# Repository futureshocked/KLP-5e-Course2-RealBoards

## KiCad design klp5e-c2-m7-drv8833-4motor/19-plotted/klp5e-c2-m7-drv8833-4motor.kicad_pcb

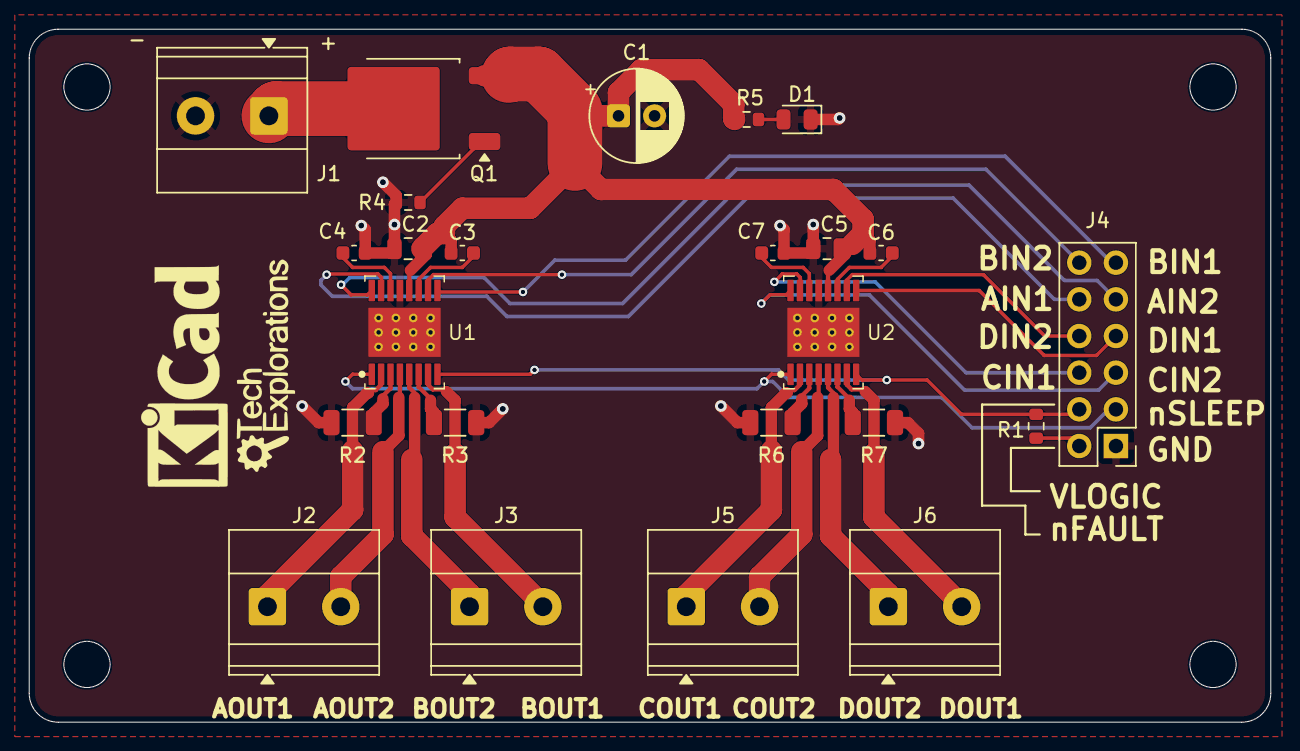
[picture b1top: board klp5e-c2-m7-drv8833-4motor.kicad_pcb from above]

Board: 2 copper layers, 86.0 x 48.0 mm, 28 parts (0 on the bottom side), 32 nets.

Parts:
C1: 100uF 25V; CP_Radial_D6.3mm_P2.50mm
C2, C5: 10uF 25V; C_0805_2012Metric
C3, C6: 0.01uF 16V; C_0603_1608Metric
C4, C7: 2.2uF 16V; C_0603_1608Metric
D1: LED; LED_0805_2012Metric
H1, H2, H3, H4: MountingHole; MountingHole_3.2mm_M3
J1, J2, J3, J5, J6: Conn_01x02; TerminalBlock_Phoenix_MKDS-1,5-2-5.08_1x02_P5.08mm_Horizont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
J4: Conn_02x06_Odd_Even; PinHeader_2x06_P2.54mm_Vertical
Q1: SUD45P03-09; TO-252-2
R1: 10k; R_0603_1608Metric
R2, R3, R6, R7: 0R2; R_1206_3216Metric
R4: 100k; R_0603_1608Metric
R5: 1k; R_0603_1608Metric
U1, U2: DRV8833; HTSSOP-16-1EP_DRV8833_PD

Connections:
/AIN1: J4.9, U1.16 (AIN1)
/AIN2: J4.10, U1.15 (AIN2)
/AISEN: R2.1, U1.3 (AISEN)
/AOUT1: J2.1, U1.2 (AOUT1)
/AOUT2: J2.2, U1.4 (AOUT2)
/BIN1: J4.11, U1.9 (BIN1)
/BIN2: J4.12, U1.10 (BIN2)
/BISEN: R3.1, U1.6 (BISEN)
/BOUT1: J3.2, U1.7 (BOUT1)
/BOUT2: J3.1, U1.5 (BOUT2)
/CIN1: J4.5, U2.16 (AIN1)
/CIN2: J4.6, U2.15 (AIN2)
/CISEN: R6.1, U2.3 (AISEN)
/COUT1: J5.1, U2.2 (AOUT1)
/COUT2: J5.2, U2.4 (AOUT2)
/DIN1: J4.7, U2.9 (BIN1)
/DIN2: J4.8, U2.10 (BIN2)
/DISEN: R7.1, U2.6 (BISEN)
/DOUT1: J6.2, U2.7 (BOUT1)
/DOUT2: J6.1, U2.5 (BOUT2)
/GATE: Q1.1 (G), R4.1
/VCP: C3.2, U1.11 (VCP)
/VCP2: C6.2, U2.11 (VCP)
/VINT: C4.2, U1.14 (VINT)
/VINT2: C7.2, U2.14 (VINT)
/VLOGIC: J4.2, R1.2
/VM: C1.1, C2.2, C3.1, C5.2, C6.1, Q1.3 (S), R5.1, U1.12 (VM), U2.12 (VM)
/VM_IN: J1.1, Q1.2 (D)
/nFAULT: J4.4, R1.1, U1.8 (nFAULT), U2.8 (nFAULT)
/nSLEEP: J4.3, U1.1 (nSLEEP), U2.1 (nSLEEP)
GND: C1.2, C2.1, C4.1, C5.1, C7.1, D1.1 (K), J1.2, J4.1, R2.2, R3.2, R4.2, R6.2, R7.2, U1.13 (GND), U1.17 (PAD), U2.13 (GND), U2.17 (PAD)
unnamed: D1.2 (A), R5.2

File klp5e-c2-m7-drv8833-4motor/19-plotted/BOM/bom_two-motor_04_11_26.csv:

"Designator","Quantity","Manufacturer Part Number","Manufacturer","Package/Footprint","Description","Procurement Type"
"J1,J2,J3","3","1715721","Phoenix Contact","TerminalBlock_Phoenix:TerminalBlock_Phoenix_MKDS-1,5-2-5.08_1x02_P5.08mm_Horizontal","Conn_01x02",""
"J5,J6","2","1715721","Phoenix Contact","TerminalBlock_Phoenix:TerminalBlock_Phoenix_MKDS-1,5-2-5.08_1x02_P5.08mm_Horizontal","Conn_01x02","DNP"
"J4","1","61301221121","Würth Elektronik","Connector_PinHeader_2.54mm:PinHeader_2x06_P2.54mm_Vertical","Conn_02x06_Odd_Even",""
"C3","1","0603YC103JAT2A","KYOCERA AVX","Capacitor_SMD:C_0603_1608Metric","0.01uF 16V",""
"C6","1","0603YC103JAT2A","KYOCERA AVX","Capacitor_SMD:C_0603_1608Metric","0.01uF 16V","DNP"
"D1","1","150080GS75000","Würth Elektronik","LED_SMD:LED_0805_2012Metric","LED",""
"R2,R3","2","CSR1206FKR200","Stackpole Electronics","Resistor_SMD:R_1206_3216Metric","0R2",""
"R6,R7","2","CSR1206FKR200","Stackpole Electronics","Resistor_SMD:R_1206_3216Metric","0R2","DNP"
"U1","1","DRV8833PWPR","Texas Instruments","peters_custom_Library:HTSSOP-16-1EP_DRV8833_PD","DRV8833",""
"U2","1","DRV8833PWPR","Texas Instruments","peters_custom_Library:HTSSOP-16-1EP_DRV8833_PD","DRV8833","DNP"
"C1","1","EEU-FR1E101","Panasonic","Capacitor_THT:CP_Radial_D6.3mm_P2.50mm","100uF 25V",""
"C4","1","EMK107BB7225KA-T","Taiyo Yuden","Capacitor_SMD:C_0603_1608Metric","2.2uF 16V",""
"C7","1","EMK107BB7225KA-T","Taiyo Yuden","Capacitor_SMD:C_0603_1608Metric","2.2uF 16V","DNP"
"C2","1","GRM21BR61E106KA73L","Murata","Capacitor_SMD:C_0805_2012Metric","10uF 25V",""
"C5","1","GRM21BR61E106KA73L","Murata","Capacitor_SMD:C_0805_2012Metric","10uF 25V","DNP"
"R5","1","RC0603FR-071KL","Yageo","Resistor_SMD:R_0603_1608Metric","1k",""
"R1","1","RC0603FR-0710KL","Yageo","Resistor_SMD:R_0603_1608Metric","10k",""
"R4","1","RC0603FR-07100KL","Yageo","Resistor_SMD:R_0603_1608Metric","100k",""
"Q1","1","SUD45P03-09-GE3","Vishay","Package_TO_SOT_SMD:TO-252-2","SUD45P03-09",""
